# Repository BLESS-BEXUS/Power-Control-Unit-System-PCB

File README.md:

<p align="center">
    <br>
    
</p>
<h1 align="center">Power Control Unit</h1>
<p align="center">
A custom PCB designed to distribute and regulate a single 28 V DC input into multiple power rails for embedded hardware systems.
</p>
<p align="center">

    <br>
    
</p>

---

### Overview

The main goal of this PCB is to provide a compact and reliable power distribution stage for embedded systems that require several regulated voltage rails from a single DC input.

The board takes a nominal 28 V DC input and generates the regulated power rails required by the system:

- 3.3 V for logic, microcontrollers and digital sensors.
- 5 V for auxiliary electronics and interface modules.
- 12 V for higher-power loads such as heaters or dedicated subsystems.

This PCB centralizes power conversion, protection and distribution, making the overall system easier to integrate, debug and maintain.

### Purpose

This board is designed to simplify power management in systems where multiple voltage levels are required from a single supply line.

It is especially useful in applications that need:

- Centralized power distribution.
- Regulated low-voltage rails.
- Separation between logic, auxiliary and high-power loads.
- Protection against electrical faults.
- Cleaner wiring between subsystems.
- Easier integration with the rest of the electronics.

### Main Features

- Single 28 V DC input.
- Regulated 3.3 V output rail.
- Regulated 5 V output rail.
- Regulated 12 V output rail.
- TRACO POWER DC/DC converters.
- Input protection stage.
- Reverse-polarity protection.
- Fuse protection.
- Decoupling and filtering capacitors.
- Dedicated outputs for different subsystem power rails.
- Custom KiCad symbols, footprints and 3D models.

---

<h3 align="center">Contributing</h3>
<p align="center">
·
    <a href="./CODE_OF_CONDUCT.md">Code of Conduct</a>
    ·
    <a href="./CONTRIBUTING.md">Contributing Guide</a>
    ·
</p>
<p align="center">We welcome collaboration from the aerospace and hardware community. For major changes or data inquiries, please open an issue first.</p>
<h3 align="center">License</h3>
<pre align="center">Copyright © 2025-2026 The BLESS Project Team<br><br>This Source Code Form is subject to the terms of the Mozilla Public<br>License, v. 2.0. If a copy of the MPL was not distributed with this<br>file, You can obtain one at http://mozilla.org/MPL/2.0/.</pre>
<h3 align="center">Credits & Team</h3>
<p align="center">Supported by the REXUS/BEXUS Program and our generous sponsors.</p>
<p align="center">
    
</p>

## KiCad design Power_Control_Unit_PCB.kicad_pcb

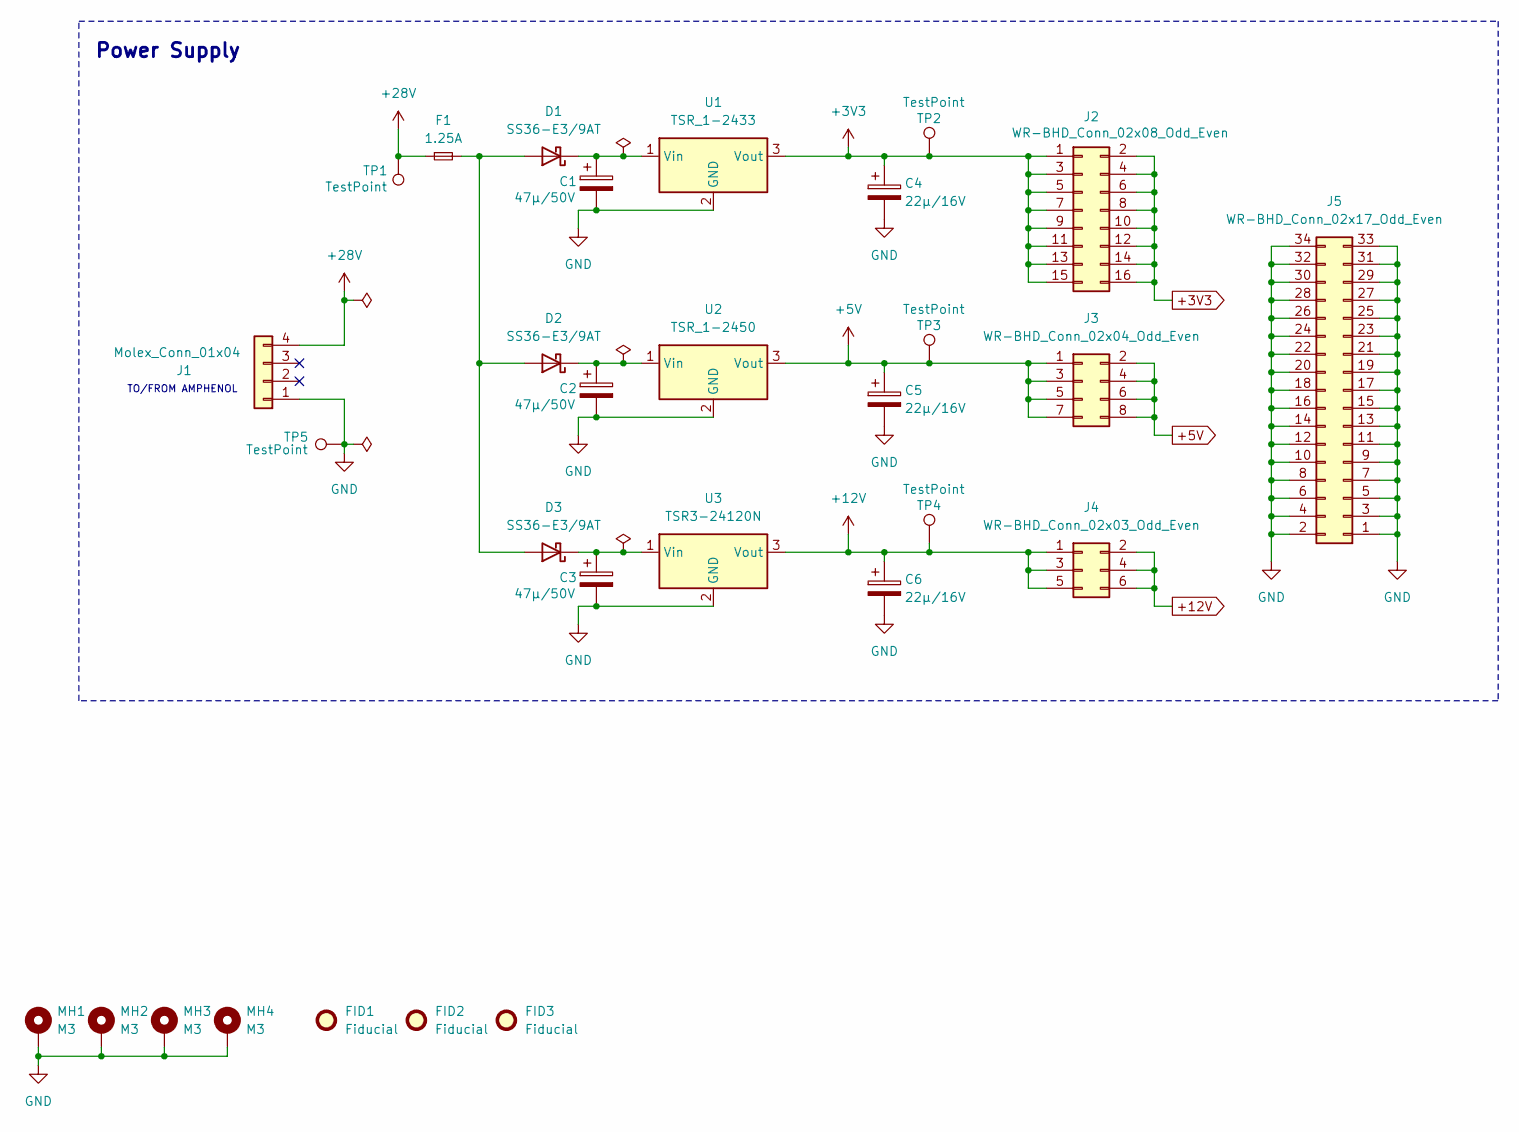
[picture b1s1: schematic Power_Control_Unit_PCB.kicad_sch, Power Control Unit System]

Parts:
C1, C2, C3: 47µ/50V; CP_Elec_6.3x7.7; Manufacturer Part Number EEE-FT1H470AP; LCSC C92059
C4, C5, C6: 22µ/16V; CP_Elec_5x5.8; Manufacturer Part Number EEE-FK1C220R; LCSC C242120
D1, D2, D3: SS36-E3/9AT; D_SMC; Manufacturer Part Number SS36-E3/9AT; LCSC C3009064
F1: 1.25A; Fuse_Littelfuse-NANO2-451_453; Manufacturer Part Number 04511.25MRL; LCSC 2410
FID1, FID2, FID3: Fiducial; Fiducial_1mm_Mask2mm
J1: Molex_Conn_01x04; Molex_Micro-Fit_3.0_43650-0415_1x04_P3.00mm_Vertical; Manufacturer Part Number 43650-0415; LCSC C293547
J2: WR-BHD_Conn_02x08_Odd_Even; IDC-Header_2x08_P2.54mm_Vertical; Manufacturer Part Number 61201621621; LCSC C3406
J3: WR-BHD_Conn_02x04_Odd_Even; IDC-Header_2x04_P2.54mm_Vertical; Manufacturer Part Number 61200821621; LCSC C9135
J4: WR-BHD_Conn_02x03_Odd_Even; IDC-Header_2x03_P2.54mm_Vertical; Manufacturer Part Number 61200621621; LCSC C11214
J5: WR-BHD_Conn_02x17_Odd_Even; IDC-Header_2x17_P2.54mm_Vertical; Manufacturer Part Number 61203421621; LCSC C20920
MH1, MH2, MH3, MH4: M3; MountingHole_3.2mm_M3_Pad_Via
TP1, TP2, TP3, TP4, TP5: TestPoint; TestPoint_Pad_D1.0mm
U1: TSR_1-2433; Converter_DCDC_TRACO_TSR-1_THT; Manufacturer Part Number TSR 1-2433; LCSC C5455553
U2: TSR_1-2450; Converter_DCDC_TRACO_TSR-1_THT; Manufacturer Part Number TSR 1-2450; LCSC C6886877
U3: TSR3-24120N; Converter_DCDC_TRACO_TSR2-24xxN_TSR2-24xxxN_THT; Manufacturer Part Number TSR 3-24120N; LCSC C45533985

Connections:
+3V3: C4.1, J2.1, J2.2, J2.3, J2.4, J2.5, J2.6, J2.7, J2.8, J2.9, J2.10, J2.11, J2.12, J2.13, J2.14, J2.15, J2.16, TP2.1 (1_1), U1.3 (Vout)
+5V: C5.1, J3.1, J3.2, J3.3, J3.4, J3.5, J3.6, J3.7, J3.8, TP3.1 (1_1), U2.3 (Vout)
+12V: C6.1, J4.1, J4.2, J4.3, J4.4, J4.5, J4.6, TP4.1 (1_1), U3.3 (Vout)
+28V: F1.1, J1.4, TP1.1 (1_1)
GND: C1.2, C2.2, C3.2, C4.2, C5.2, C6.2, J1.1, J5.1, J5.2, J5.3, J5.4, J5.5, J5.6, J5.7, J5.8, J5.9, J5.10, J5.11, J5.12, J5.13, J5.14, J5.15, J5.16, J5.17, J5.18, J5.19, J5.20, J5.21, J5.22, J5.23, J5.24, J5.25, J5.26, J5.27, J5.28, J5.29, J5.30, J5.31, J5.32, J5.33, J5.34, MH1.1 (1_1), MH2.1 (1_1), MH3.1 (1_1), MH4.1 (1_1), TP5.1 (1_1), U1.2 (GND), U2.2 (GND), U3.2 (GND)
unnamed: D1.2 (A), D2.2 (A), D3.2 (A), F1.2
unnamed: C1.1, D1.1 (K), U1.1 (Vin)
unnamed: C2.1, D2.1 (K), U2.1 (Vin)
unnamed: C3.1, D3.1 (K), U3.1 (Vin)

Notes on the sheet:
TO/FROM AMPHENOL
Power Supply

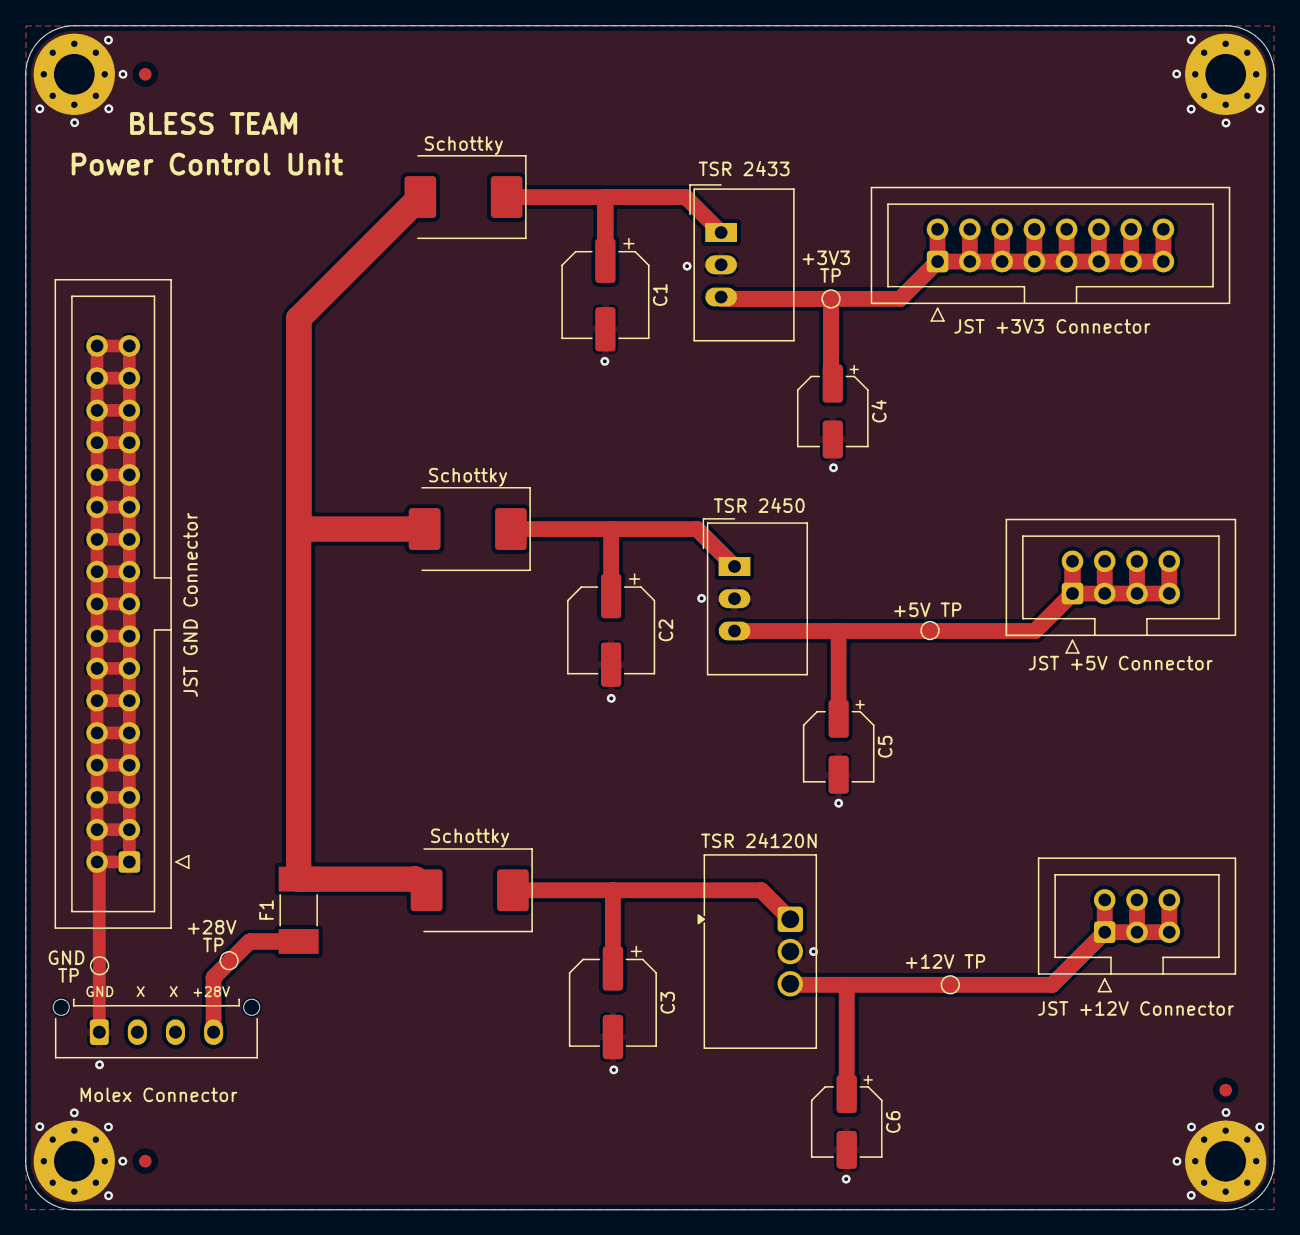
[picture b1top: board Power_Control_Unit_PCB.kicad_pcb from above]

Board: 2 copper layers, 98.3 x 93.2 mm, 30 parts (0 on the bottom side), 9 nets.

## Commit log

2026-06-14 Add .DS_Store to .gitignore to exclude MacOS metadata files
2026-06-14 Add project README
2026-06-14 Add project KiCad initial files
2026-06-14 PCU Schematics
2026-06-14 PCU Initial PCB design and routing
2026-06-14 PCU pcb design and added copper zones por power planes
